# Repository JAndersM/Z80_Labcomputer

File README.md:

# Z80_Labcomputer

A computerproject based on the Z80 CPU.

## Dator
Motherboard with Z80, 8 kB ROM and 32 kB SRAM, IO ports, Bus ports etc.
* Schema, PCB designed
* Produced and tested. OK so far...

## cpukontroll
Clock, Reset etc.
* Schema, PCB design

## display
7x4-segment display and IO-connections to adress 0-3
* Schema PCB design

## tangentbord
Hex values input keyboard
* Schema, PCB design
Needs redesign

## EEPROMprogrammer
Arduino code and design for an Arduino Nano (or similar) based EEPROMprogrammer
* Schema, PCB design
Connected to the computer using BUSRQ to facilitate programming without removing ROM.

## simulering
Python simulation of the z80 cpu and the computer
* Inkludes 7x4 display
Many opcodes not simulated yet

## fastplatta
Holder for the Dator PCB
* 3D printed and tested

## Used software:
KiCad, FreeCAD, Python, Arduino IDE

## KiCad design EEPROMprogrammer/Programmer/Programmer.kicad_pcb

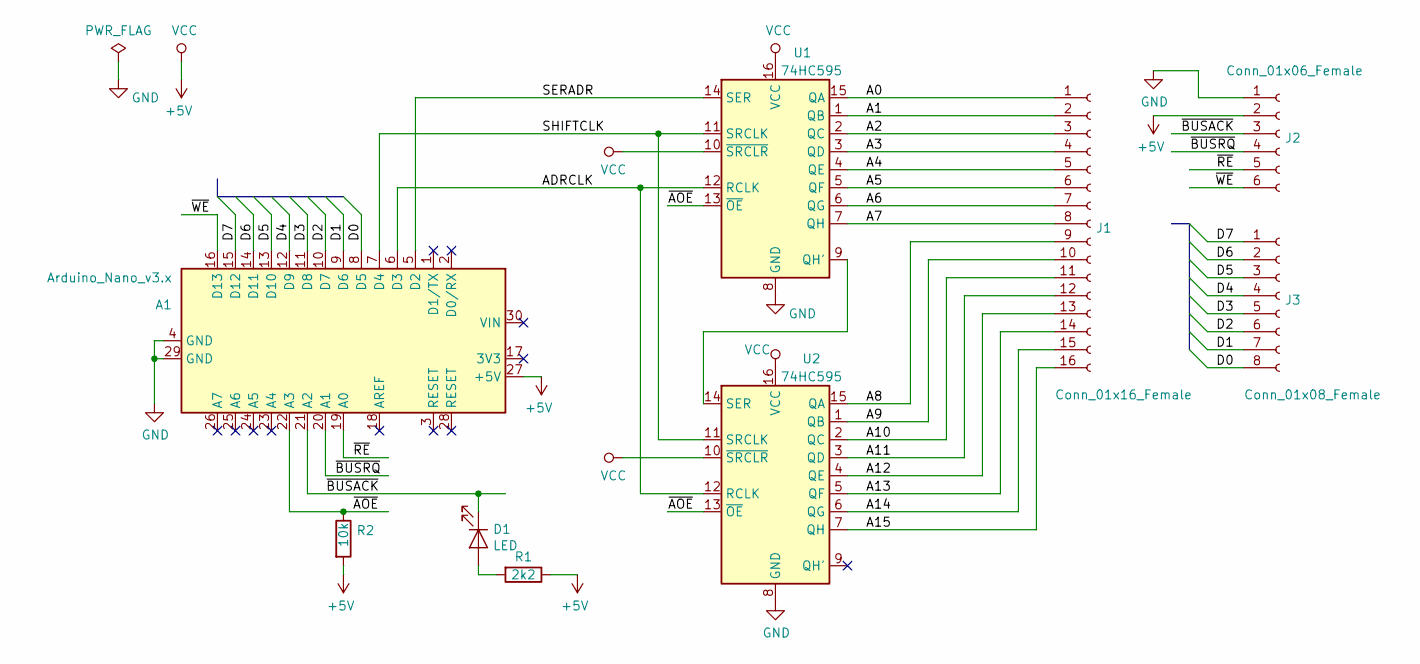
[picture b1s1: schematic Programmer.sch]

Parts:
A1: Arduino_Nano_v3.x; Arduino_Nano
D1: LED; LED_D3.0mm
J1: Conn_01x16_Female; PinSocket_1x16_P2.54mm_Vertical
J2: Conn_01x06_Female; PinSocket_1x06_P2.54mm_Vertical
J3: Conn_01x08_Female; PinSocket_1x08_P2.54mm_Vertical
R1: 2k2; R_Axial_DIN0207_L6.3mm_D2.5mm_P7.62mm_Horizontal
R2: 10k; R_Axial_DIN0207_L6.3mm_D2.5mm_P7.62mm_Horizontal
U1, U2: 74HC595; DIP-16_W7.62mm

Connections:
+5V: A1.27 (+5V), J2.2, R1.1, R2.2, U1.10 (~SRCLR), U1.16 (VCC), U2.10 (~SRCLR), U2.16 (VCC)
/A0: J1.1, U1.15 (QA)
/A1: J1.2, U1.1 (QB)
/A2: J1.3, U1.2 (QC)
/A3: J1.4, U1.3 (QD)
/A4: J1.5, U1.4 (QE)
/A5: J1.6, U1.5 (QF)
/A6: J1.7, U1.6 (QG)
/A7: J1.8, U1.7 (QH)
/A8: J1.9, U2.15 (QA)
/A9: J1.10, U2.1 (QB)
/A10: J1.11, U2.2 (QC)
/A11: J1.12, U2.3 (QD)
/A12: J1.13, U2.4 (QE)
/A13: J1.14, U2.5 (QF)
/A14: J1.15, U2.6 (QG)
/A15: J1.16, U2.7 (QH)
/ADRCLK: A1.6 (D3), U1.12 (RCLK), U2.12 (RCLK)
/D0: A1.8 (D5), J3.8
/D1: A1.9 (D6), J3.7
/D2: A1.10 (D7), J3.6
/D3: A1.11 (D8), J3.5
/D4: A1.12 (D9), J3.4
/D5: A1.13 (D10), J3.3
/D6: A1.14 (D11), J3.2
/D7: A1.15 (D12), J3.1
/SERADR: A1.5 (D2), U1.14 (SER)
/SHIFTCLK: A1.7 (D4), U1.11 (SRCLK), U2.11 (SRCLK)
/~AOE: A1.22 (A3), R2.1, U1.13 (~OE), U2.13 (~OE)
/~BUSACK: A1.21 (A2), D1.1 (K), J2.3
/~BUSRQ: A1.20 (A1), J2.4
/~RE: A1.19 (A0), J2.5
/~WE: A1.16 (D13), J2.6
GND: A1.4 (GND), A1.29 (GND), J2.1, U1.8 (GND), U2.8 (GND)
unnamed: D1.2 (A), R1.2
unnamed: U1.9 (QH'), U2.14 (SER)

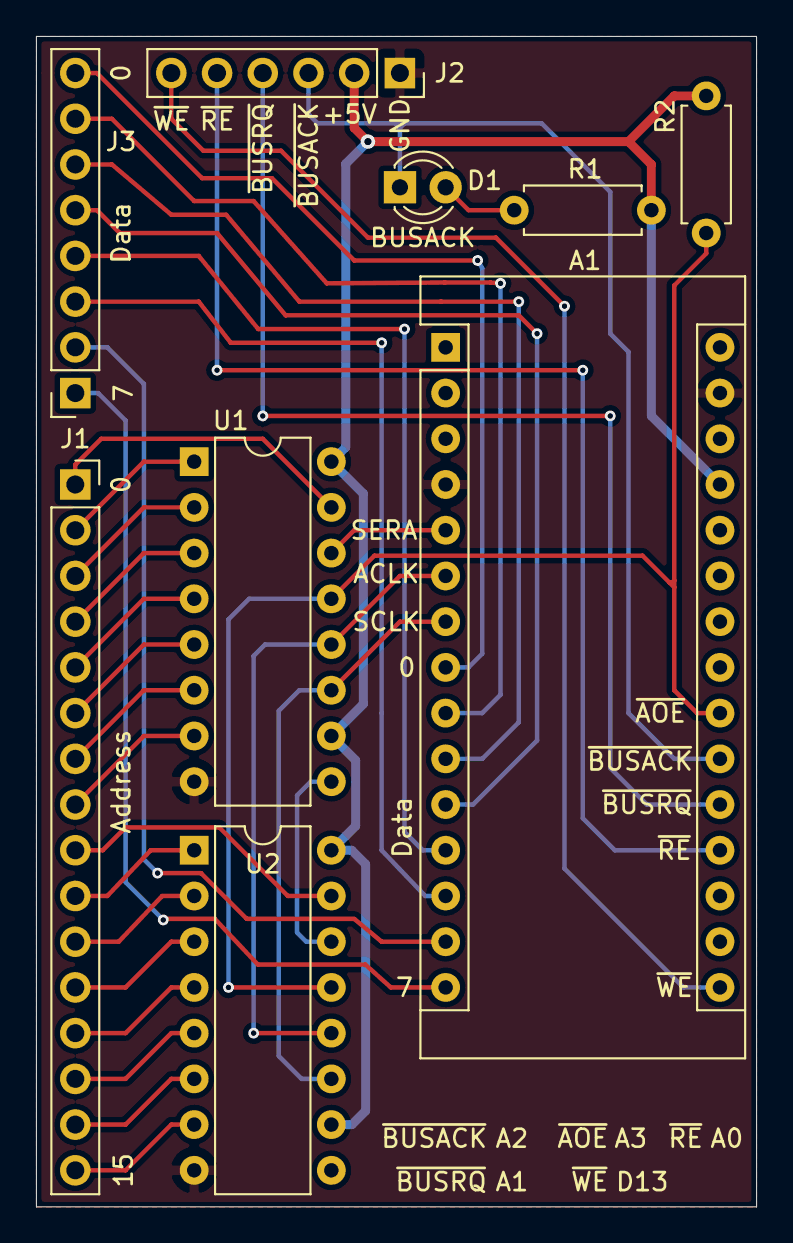
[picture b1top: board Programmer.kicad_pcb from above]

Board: 2 copper layers, 40.0 x 65.0 mm, 9 parts (0 on the bottom side), 36 nets.

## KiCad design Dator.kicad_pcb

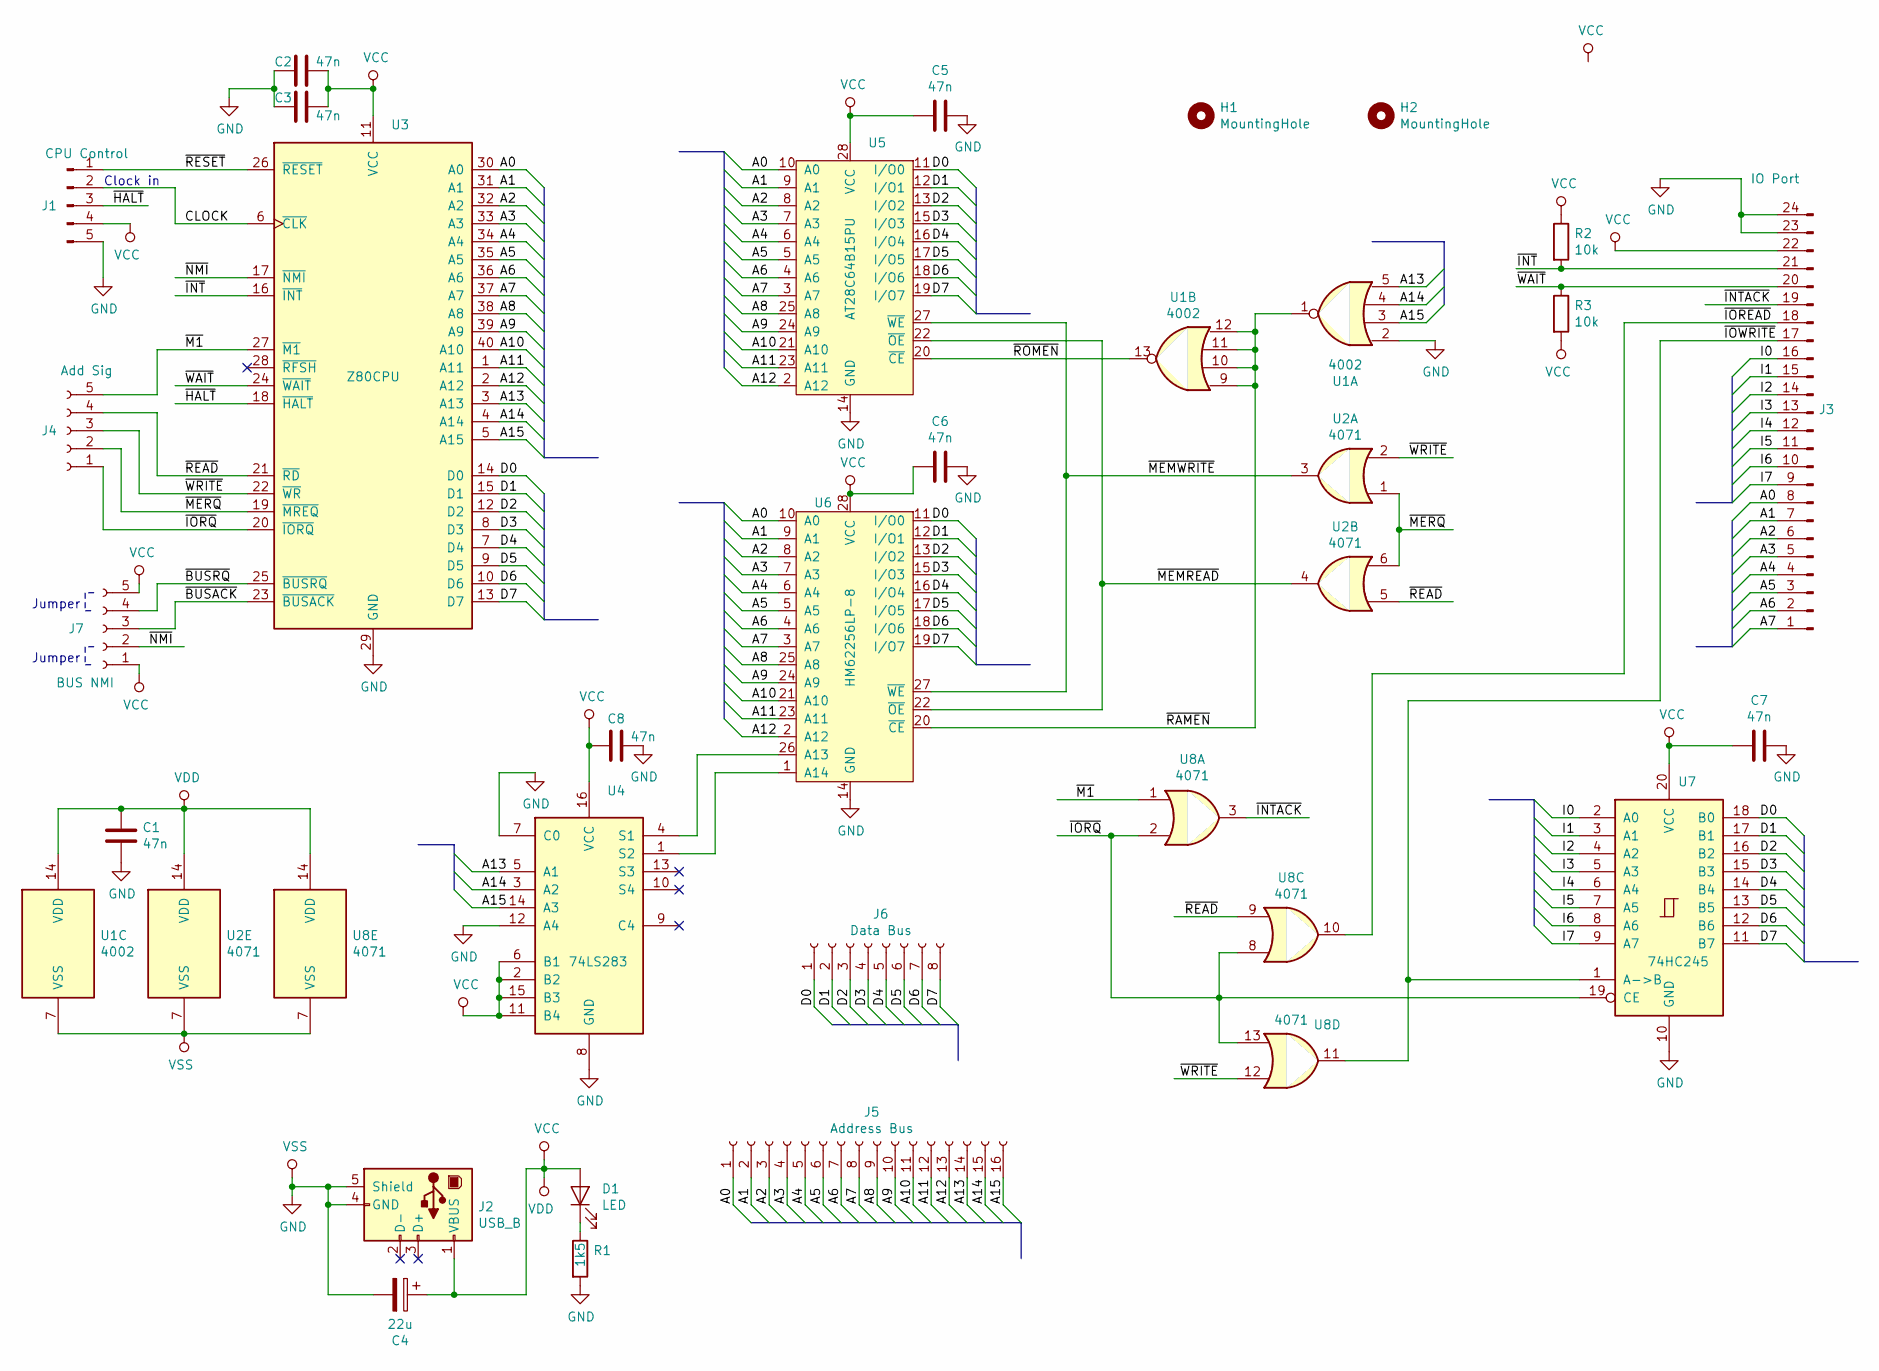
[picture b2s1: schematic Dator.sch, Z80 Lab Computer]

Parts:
C1, C2, C3, C5, C6, C7, C8: 47n; C_Disc_D3.0mm_W1.6mm_P2.50mm
C4: 22u; C_Radial_D5.0mm_H11.0mm_P2.00mm
D1: LED; LED_D3.0mm
H1, H2: MountingHole; MountingHole_2.2mm_M2
J1: CPU Control; PinHeader_1x05_P2.54mm_Vertical
J2: USB_B; USB_B_OST_USB-B1HSxx_Horizontal
J3: IO Port; PinHeader_1x24_P2.54mm_Vertical
J4: Add Sig; PinSocket_1x05_P2.54mm_Vertical
J5: Address Bus; PinSocket_1x16_P2.54mm_Vertical
J6: Data Bus; PinSocket_1x08_P2.54mm_Vertical
J7: BUS NMI; PinSocket_1x05_P2.54mm_Vertical
R1: 1k5; R_Axial_DIN0207_L6.3mm_D2.5mm_P7.62mm_Horizontal
R2, R3: 10k; R_Axial_DIN0207_L6.3mm_D2.5mm_P7.62mm_Horizontal
U1: 4002; DIP-14_W7.62mm
U2, U8: 4071; DIP-14_W7.62mm
U3: Z80CPU; DIP-40_W15.24mm_Socket
U4: 74LS283; DIP-16_W7.62mm
U5: AT28C64B15PU; DIP-28_W15.24mm_Socket
U6: HM62256LP-8; DIP-28_W15.24mm_Socket
U7: 74HC245; DIP-20_W7.62mm

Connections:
/A0: J3.8, J5.1, U3.30 (A0), U5.10 (A0), U6.10 (A0)
/A1: J3.7, J5.2, U3.31 (A1), U5.9 (A1), U6.9 (A1)
/A2: J3.6, J5.3, U3.32 (A2), U5.8 (A2), U6.8 (A2)
/A3: J3.5, J5.4, U3.33 (A3), U5.7 (A3), U6.7 (A3)
/A4: J3.4, J5.5, U3.34 (A4), U5.6 (A4), U6.6 (A4)
/A5: J3.3, J5.6, U3.35 (A5), U5.5 (A5), U6.5 (A5)
/A6: J3.2, J5.7, U3.36 (A6), U5.4 (A6), U6.4 (A6)
/A7: J3.1, J5.8, U3.37 (A7), U5.3 (A7), U6.3 (A7)
/A8: J5.9, U3.38 (A8), U5.25 (A8), U6.25 (A8)
/A9: J5.10, U3.39 (A9), U5.24 (A9), U6.24 (A9)
/A10: J5.11, U3.40 (A10), U5.21 (A10), U6.21 (A10)
/A11: J5.12, U3.1 (A11), U5.23 (A11), U6.23 (A11)
/A12: J5.13, U3.2 (A12), U5.2 (A12), U6.2 (A12)
/A13: J5.14, U1.5, U3.3 (A13), U4.5 (A1)
/A14: J5.15, U1.4, U3.4 (A14), U4.3 (A2)
/A15: J5.16, U1.3, U3.5 (A15), U4.14 (A3)
/CLOCK: J1.2, U3.6 (~CLK~)
/D0: J6.1, U3.14 (D0), U5.11 (I/O0), U6.11 (I/O0), U7.18 (B0)
/D1: J6.2, U3.15 (D1), U5.12 (I/O1), U6.12 (I/O1), U7.17 (B1)
/D2: J6.3, U3.12 (D2), U5.13 (I/O2), U6.13 (I/O2), U7.16 (B2)
/D3: J6.4, U3.8 (D3), U5.15 (I/O3), U6.15 (I/O3), U7.15 (B3)
/D4: J6.5, U3.7 (D4), U5.16 (I/O4), U6.16 (I/O4), U7.14 (B4)
/D5: J6.6, U3.9 (D5), U5.17 (I/O5), U6.17 (I/O5), U7.13 (B5)
/D6: J6.7, U3.10 (D6), U5.18 (I/O6), U6.18 (I/O6), U7.12 (B6)
/D7: J6.8, U3.13 (D7), U5.19 (I/O7), U6.19 (I/O7), U7.11 (B7)
/I0: J3.16, U7.2 (A0)
/I1: J3.15, U7.3 (A1)
/I2: J3.14, U7.4 (A2)
/I3: J3.13, U7.5 (A3)
/I4: J3.12, U7.6 (A4)
/I5: J3.11, U7.7 (A5)
/I6: J3.10, U7.8 (A6)
/I7: J3.9, U7.9 (A7)
/~BUSACK: J7.3, U3.23 (~BUSACK~)
/~BUSRQ: J7.4, U3.25 (~BUSRQ~)
/~HALT: J1.3, U3.18 (~HALT~)
/~INT: J3.21, R2.2, U3.16 (~INT~)
/~INTACK: J3.19, U8.3
/~IOREAD: J3.18, U8.10
/~IORQ: J4.1, U3.20 (~IORQ~), U7.19 (CE), U8.2, U8.8, U8.13
/~IOWRITE: J3.17, U7.1 (A->B), U8.11
/~M1: J4.5, U3.27 (~M1~), U8.1
/~MEMREAD: U2.4, U5.22 (~OE), U6.22 (~OE)
/~MEMWRITE: U2.3, U5.27 (~WE), U6.27 (~WE)
/~MERQ: J4.2, U2.1, U2.6, U3.19 (~MREQ~)
/~NMI: J7.2, U3.17 (~NMI~)
/~RAMEN: U1.1, U1.9, U1.10, U1.11, U1.12, U6.20 (~CE)
/~READ: J4.4, U2.5, U3.21 (~RD~), U8.9
/~RESET: J1.1, U3.26 (~RESET~)
/~ROMEN: U1.13, U5.20 (~CE)
/~WAIT: J3.20, R3.1, U3.24 (~WAIT~)
/~WRITE: J4.3, U2.2, U3.22 (~WR~), U8.12
GND: C1.2, C2.2, C3.2, C4.2, C5.1, C6.1, C7.1, C8.1, J1.5, J2.4 (GND), J2.5 (Shield), J3.23, J3.24, R1.2, U1.2, U1.7 (VSS), U2.7 (VSS), U3.29 (GND), U4.7 (C0), U4.8 (GND), U4.12 (A4), U5.14 (GND), U6.14 (GND), U7.10 (GND), U8.7 (VSS)
unnamed: D1.1 (K), R1.1
unnamed: U4.1 (S2), U6.1 (A14)
unnamed: U4.4 (S1), U6.26 (A13)
VCC: C1.1, C2.1, C3.1, C4.1, C5.2, C6.2, C7.2, C8.2, D1.2 (A), J1.4, J2.1 (VBUS), J3.22, J7.1, J7.5, R2.1, R3.2, U1.14 (VDD), U2.14 (VDD), U3.11 (VCC), U4.2 (B2), U4.6 (B1), U4.11 (B4), U4.15 (B3), U4.16 (VCC), U5.28 (VCC), U6.28 (VCC), U7.20 (VCC), U8.14 (VDD)

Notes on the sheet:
Clock in
Jumper

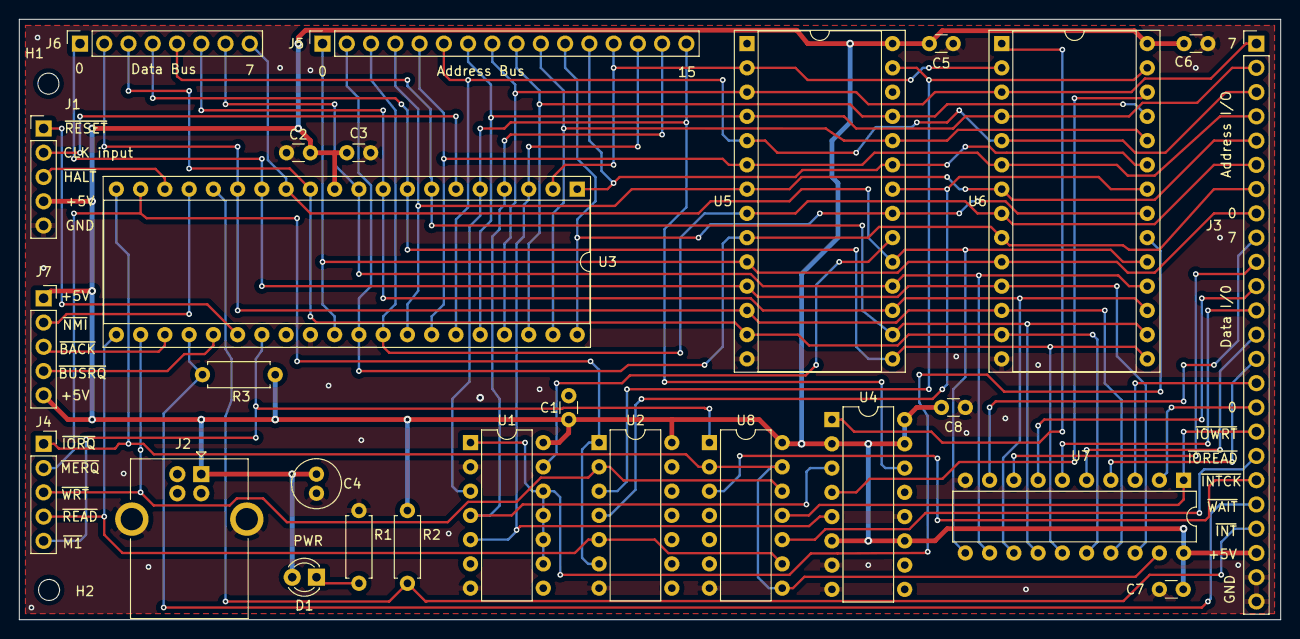
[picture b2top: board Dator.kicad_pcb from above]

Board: 2 copper layers, 132.1 x 62.9 mm, 29 parts (0 on the bottom side), 57 nets.

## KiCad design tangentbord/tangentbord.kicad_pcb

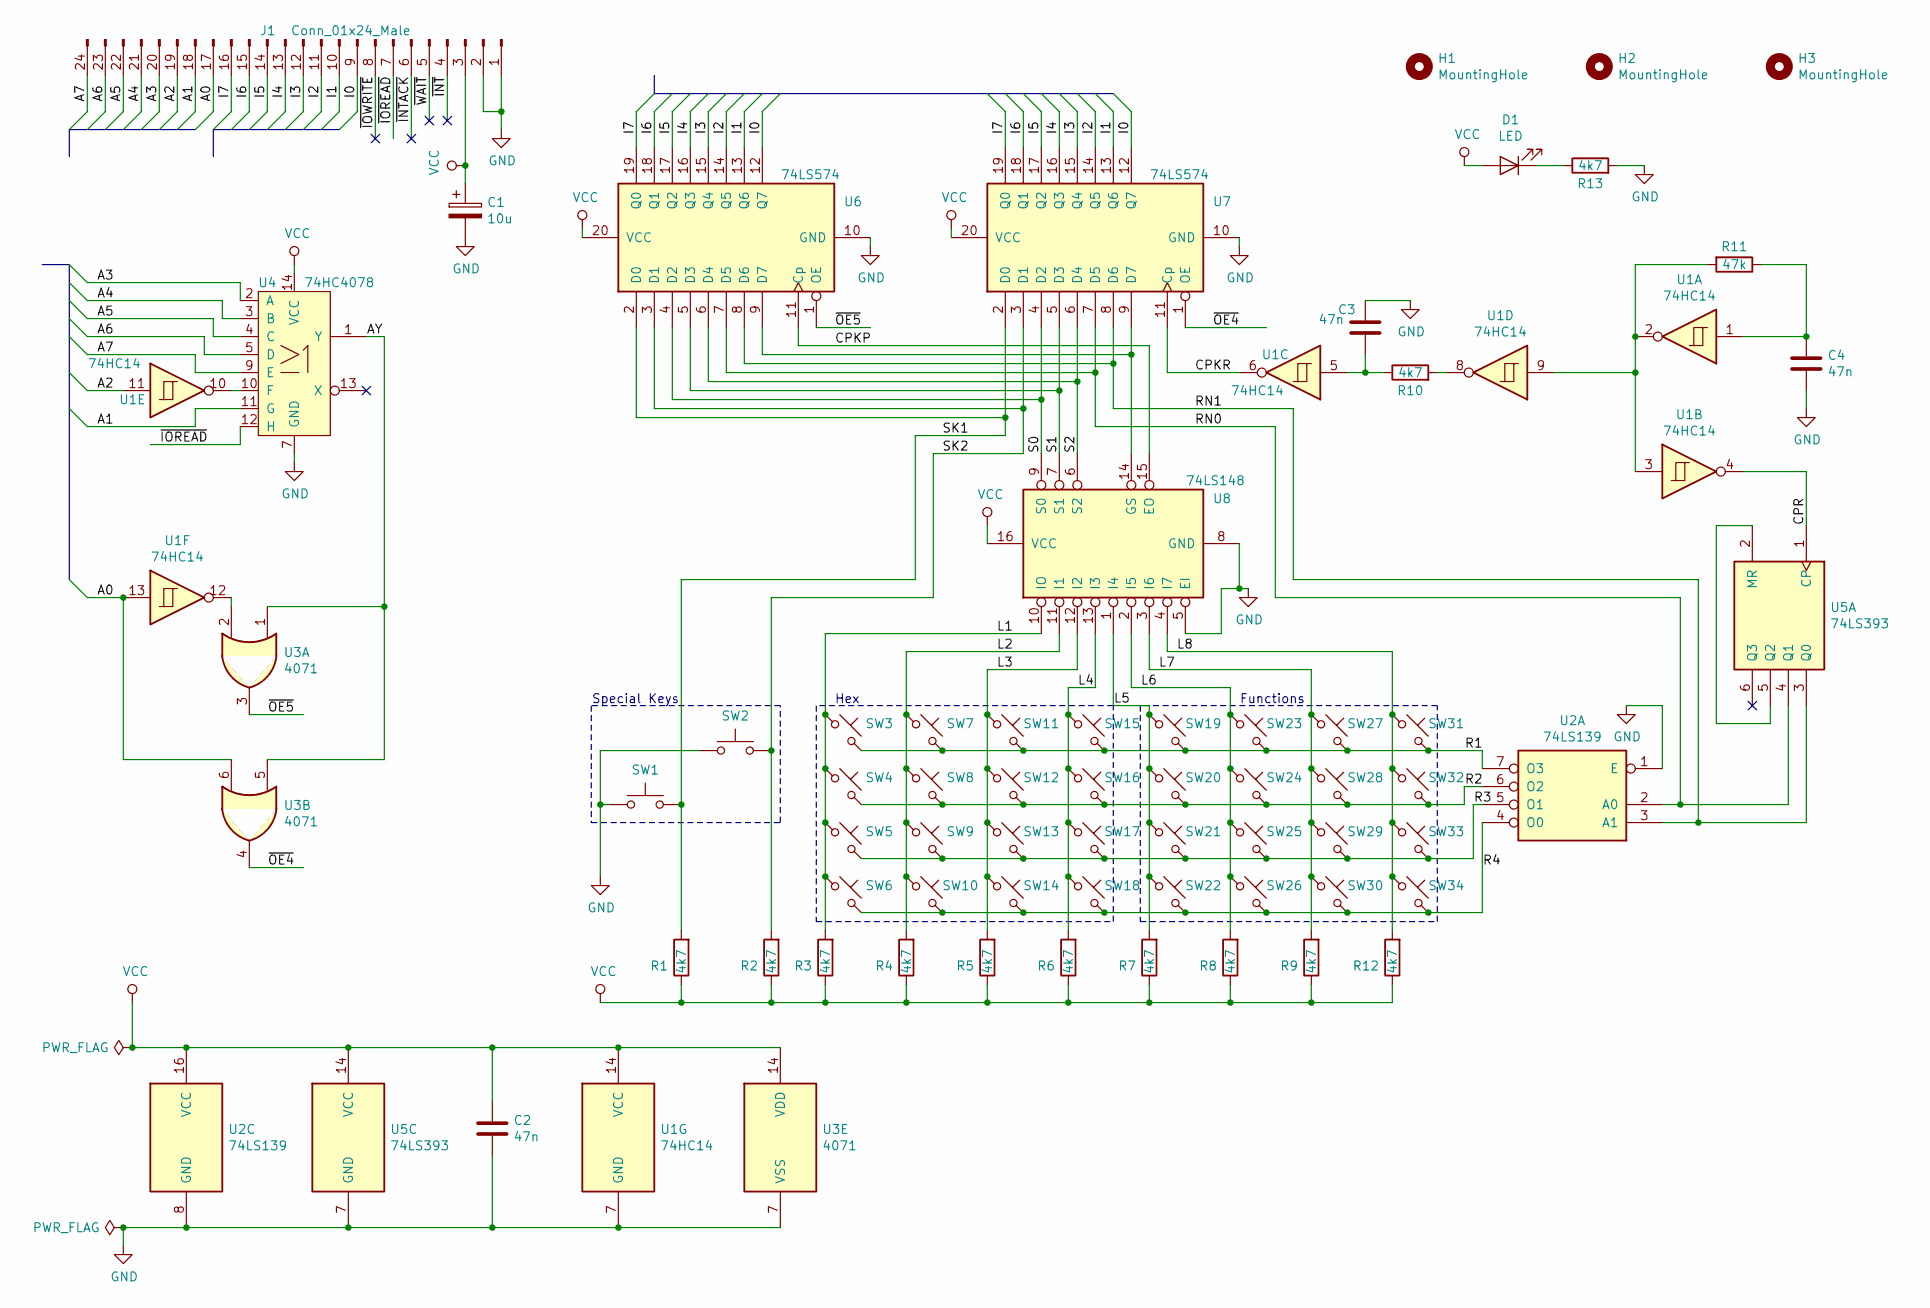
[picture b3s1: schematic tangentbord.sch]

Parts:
C1: 10u; CP_Radial_D5.0mm_P2.00mm
C2, C3, C4: 47n; C_Disc_D3.0mm_W2.0mm_P2.50mm
D1: LED; LED_D3.0mm
H1, H2, H3: MountingHole; MountingHole_2.2mm_M2
J1: Conn_01x24_Male; PinHeader_1x24_P2.54mm_Vertical
R1, R2, R3, R4, R5, R6, R7, R8, R9, R10, R12, R13: 4k7; R_Axial_DIN0207_L6.3mm_D2.5mm_P7.62mm_Horizontal
R11: 47k; R_Axial_DIN0207_L6.3mm_D2.5mm_P7.62mm_Horizontal
SW1, SW2: SW_Push; SW_PUSH_6mm
SW3, SW4, SW5, SW6, SW7, SW8, SW9, SW10, SW11, SW12, SW13, SW14, SW15, SW16, SW17, SW18, SW19, SW20, SW21, SW22, SW23, SW24, SW25, SW26, SW27, SW28, SW29, SW30, SW31, SW32, SW33, SW34: SW_Push_45deg; SW_PUSH_6mm
U1: 74HC14; DIP-14_W7.62mm
U2: 74LS139; DIP-16_W7.62mm
U3: 4071; DIP-14_W7.62mm
U4: 74HC4078; DIP-14_W7.62mm
U5: 74LS393; DIP-14_W7.62mm
U6, U7: 74LS574; DIP-20_W7.62mm
U8: 74LS148; DIP-16_W7.62mm

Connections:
/A0: J1.17, U1.13, U3.6
/A1: J1.18, U4.11 (G)
/A2: J1.19, U1.11
/A3: J1.20, U4.2 (A)
/A4: J1.21, U4.3 (B)
/A5: J1.22, U4.4 (C)
/A6: J1.23, U4.5 (D)
/A7: J1.24, U4.9 (E)
/AY: U3.1, U3.5, U4.1 (Y)
/CPKP: U6.11 (Cp), U8.15 (EO)
/CPKR: U1.6, U7.11 (Cp)
/CPR: U1.4, U5.1 (CP)
/I0: J1.9, U6.12 (Q7), U7.12 (Q7)
/I1: J1.10, U6.13 (Q6), U7.13 (Q6)
/I2: J1.11, U6.14 (Q5), U7.14 (Q5)
/I3: J1.12, U6.15 (Q4), U7.15 (Q4)
/I4: J1.13, U6.16 (Q3), U7.16 (Q3)
/I5: J1.14, U6.17 (Q2), U7.17 (Q2)
/I6: J1.15, U6.18 (Q1), U7.18 (Q1)
/I7: J1.16, U6.19 (Q0), U7.19 (Q0)
/L1: R3.2, SW3.1, SW4.1, SW5.1, SW6.1, U8.10 (IO)
/L2: R4.2, SW7.1, SW8.1, SW9.1, SW10.1, U8.11 (I1)
/L3: R5.2, SW11.1, SW12.1, SW13.1, SW14.1, U8.12 (I2)
/L4: R6.2, SW15.1, SW16.1, SW17.1, SW18.1, U8.13 (I3)
/L5: R7.2, SW19.1, SW20.1, SW21.1, SW22.1, U8.1 (I4)
/L6: R8.2, SW23.1, SW24.1, SW25.1, SW26.1, U8.2 (I5)
/L7: R9.2, SW27.1, SW28.1, SW29.1, SW30.1, U8.3 (I6)
/L8: R12.2, SW31.1, SW32.1, SW33.1, SW34.1, U8.4 (I7)
/R1: SW3.2, SW7.2, SW11.2, SW15.2, SW19.2, SW23.2, SW27.2, SW31.2, U2.7 (O3)
/R2: SW4.2, SW8.2, SW12.2, SW16.2, SW20.2, SW24.2, SW28.2, SW32.2, U2.6 (O2)
/R3: SW5.2, SW9.2, SW13.2, SW17.2, SW21.2, SW25.2, SW29.2, SW33.2, U2.5 (O1)
/R4: SW6.2, SW10.2, SW14.2, SW18.2, SW22.2, SW26.2, SW30.2, SW34.2, U2.4 (O0)
/RN0: U2.2 (A0), U5.4 (Q1), U6.7 (D5), U7.7 (D5)
/RN1: U2.3 (A1), U5.3 (Q0), U6.8 (D6), U7.8 (D6)
/S0: U6.4 (D2), U7.4 (D2), U8.9 (S0)
/S1: U6.5 (D3), U7.5 (D3), U8.7 (S1)
/S2: U6.6 (D4), U7.6 (D4), U8.6 (S2)
/SK1: R1.2, SW1.2, U6.2 (D0), U7.2 (D0)
/SK2: R2.2, SW2.2, U6.3 (D1), U7.3 (D1)
/~INT: J1.4
/~INTACK: J1.6
/~IOREAD: J1.7, U4.12 (H)
/~IOWRITE: J1.8
/~OE4: U3.4, U7.1 (OE)
/~OE5: U3.3, U6.1 (OE)
/~WAIT: J1.5
GND: C1.2, C2.2, C3.2, C4.2, J1.1, J1.2, R13.2, SW1.1, SW2.1, U1.7 (GND), U2.1 (E), U2.8 (GND), U3.7 (VSS), U4.7 (GND), U5.7 (GND), U6.10 (GND), U7.10 (GND), U8.5 (EI), U8.8 (GND)
unnamed: C3.1, R10.1, U1.5
unnamed: C4.1, R11.1, U1.1
unnamed: D1.1 (K), R13.1
unnamed: R10.2, U1.8
unnamed: R11.2, U1.2, U1.3, U1.9
unnamed: U1.10, U4.10 (F)
unnamed: U1.12, U3.2
unnamed: U5.2 (MR), U5.5 (Q2)
unnamed: U6.9 (D7), U7.9 (D7), U8.14 (GS)
VCC: C1.1, C2.1, D1.2 (A), J1.3, R1.1, R2.1, R3.1, R4.1, R5.1, R6.1, R7.1, R8.1, R9.1, R12.1, U1.14 (VCC), U2.16 (VCC), U3.14 (VDD), U4.14 (VCC), U5.14 (VCC), U6.20 (VCC), U7.20 (VCC), U8.16 (VCC)

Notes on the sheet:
Special Keys
Hex
Functions

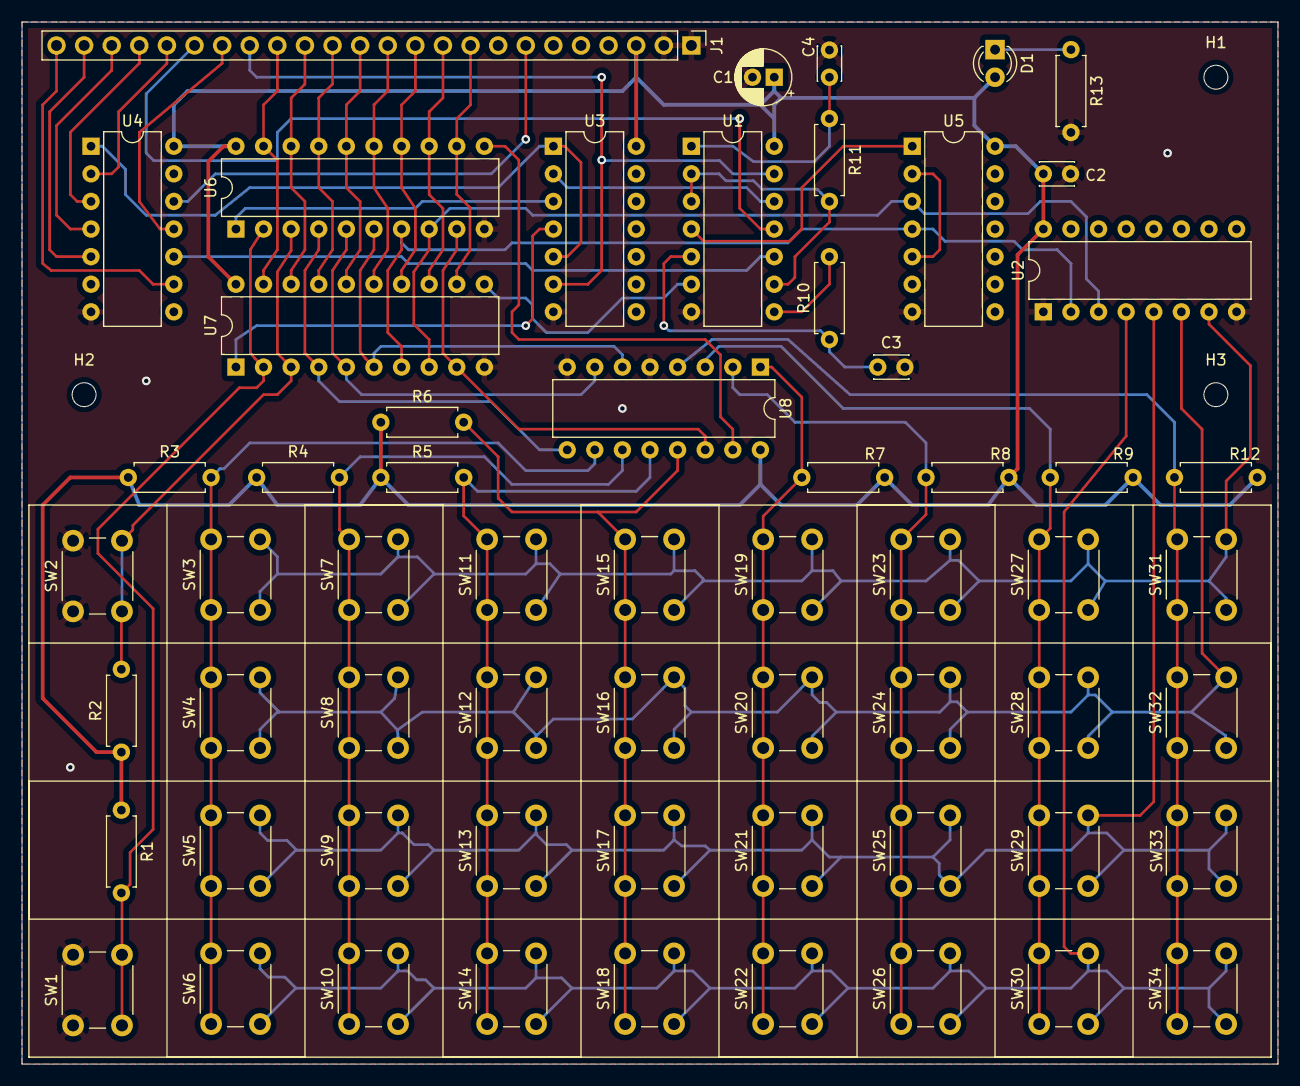
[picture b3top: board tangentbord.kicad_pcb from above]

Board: 2 copper layers, 115.6 x 95.9 mm, 64 parts (0 on the bottom side), 53 nets.

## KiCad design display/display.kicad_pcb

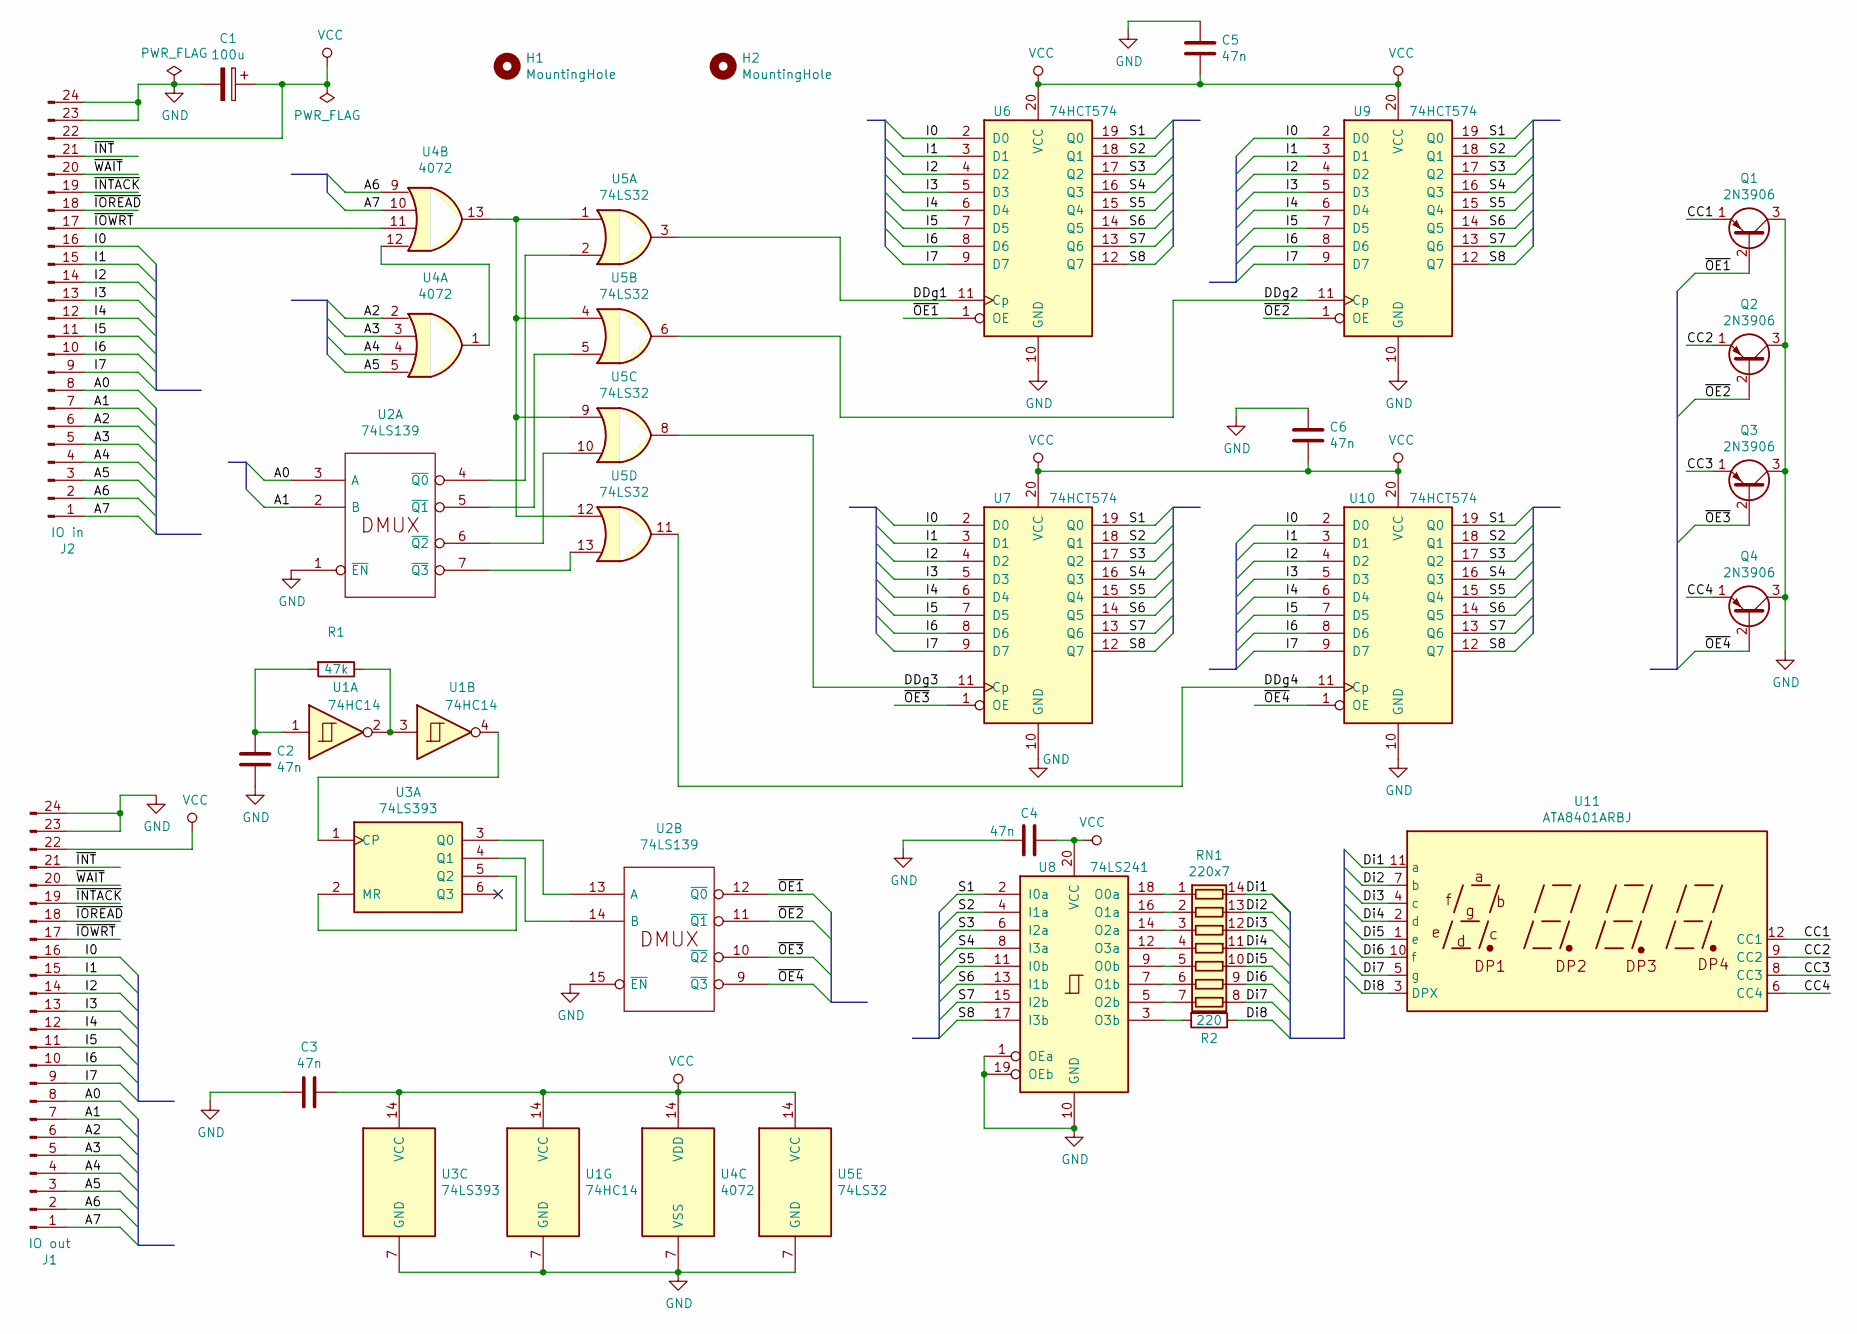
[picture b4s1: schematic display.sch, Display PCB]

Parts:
C1: 100u; CP_Radial_D6.3mm_P2.50mm
C2, C3, C4, C5, C6: 47n; C_Disc_D3.0mm_W1.6mm_P2.50mm
H1, H2: MountingHole; MountingHole_2.2mm_M2
J1: IO out; PinHeader_1x24_P2.54mm_Vertical
J2: IO in; PinHeader_1x24_P2.54mm_Vertical
Q1, Q2, Q3, Q4: 2N3906; TO-92L_Inline_Wide
R1: 47k; R_Axial_DIN0207_L6.3mm_D2.5mm_P7.62mm_Horizontal
R2: 220; R_Axial_DIN0207_L6.3mm_D2.5mm_P7.62mm_Horizontal
RN1: 220x7; DIP-14_W7.62mm
U1: 74HC14; DIP-14_W7.62mm
U2: 74LS139; DIP-16_W7.62mm
U3: 74LS393; DIP-14_W7.62mm
U4: 4072; DIP-14_W7.62mm
U5: 74LS32; DIP-14_W7.62mm
U6, U7, U9, U10: 74HCT574; DIP-20_W7.62mm
U8: 74LS241; DIP-20_W7.62mm
U11: ATA8401ARBJ

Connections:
/A0: J1.8, J2.8, U2.3 (A)
/A1: J1.7, J2.7, U2.2 (B)
/A2: J1.6, J2.6, U4.2
/A3: J1.5, J2.5, U4.3
/A4: J1.4, J2.4, U4.4
/A5: J1.3, J2.3, U4.5
/A6: J1.2, J2.2, U4.9
/A7: J1.1, J2.1, U4.10
/CC1: Q1.1 (E), U11.12 (CC1)
/CC2: Q2.1 (E), U11.9 (CC2)
/CC3: Q3.1 (E), U11.8 (CC3)
/CC4: Q4.1 (E), U11.6 (CC4)
/DDg1: U5.3, U6.11 (Cp)
/DDg2: U5.6, U9.11 (Cp)
/DDg3: U5.8, U7.11 (Cp)
/DDg4: U5.11, U10.11 (Cp)
/Di1: RN1.14 (R1.2), U11.11 (a)
/Di2: RN1.13 (R2.2), U11.7 (b)
/Di3: RN1.12 (R3.2), U11.4 (c)
/Di4: RN1.11 (R4.2), U11.2 (d)
/Di5: RN1.10 (R5.2), U11.1 (e)
/Di6: RN1.9 (R6.2), U11.10 (f)
/Di7: RN1.8 (R7.2), U11.5 (g)
/Di8: R2.1, U11.3 (DPX)
/I0: J1.16, J2.16, U6.2 (D0), U7.2 (D0), U9.2 (D0), U10.2 (D0)
/I1: J1.15, J2.15, U6.3 (D1), U7.3 (D1), U9.3 (D1), U10.3 (D1)
/I2: J1.14, J2.14, U6.4 (D2), U7.4 (D2), U9.4 (D2), U10.4 (D2)
/I3: J1.13, J2.13, U6.5 (D3), U7.5 (D3), U9.5 (D3), U10.5 (D3)
/I4: J1.12, J2.12, U6.6 (D4), U7.6 (D4), U9.6 (D4), U10.6 (D4)
/I5: J1.11, J2.11, U6.7 (D5), U7.7 (D5), U9.7 (D5), U10.7 (D5)
/I6: J1.10, J2.10, U6.8 (D6), U7.8 (D6), U9.8 (D6), U10.8 (D6)
/I7: J1.9, J2.9, U6.9 (D7), U7.9 (D7), U9.9 (D7), U10.9 (D7)
/S1: U6.19 (Q0), U7.19 (Q0), U8.2 (I0a), U9.19 (Q0), U10.19 (Q0)
/S2: U6.18 (Q1), U7.18 (Q1), U8.4 (I1a), U9.18 (Q1), U10.18 (Q1)
/S3: U6.17 (Q2), U7.17 (Q2), U8.6 (I2a), U9.17 (Q2), U10.17 (Q2)
/S4: U6.16 (Q3), U7.16 (Q3), U8.8 (I3a), U9.16 (Q3), U10.16 (Q3)
/S5: U6.15 (Q4), U7.15 (Q4), U8.11 (I0b), U9.15 (Q4), U10.15 (Q4)
/S6: U6.14 (Q5), U7.14 (Q5), U8.13 (I1b), U9.14 (Q5), U10.14 (Q5)
/S7: U6.13 (Q6), U7.13 (Q6), U8.15 (I2b), U9.13 (Q6), U10.13 (Q6)
/S8: U6.12 (Q7), U7.12 (Q7), U8.17 (I3b), U9.12 (Q7), U10.12 (Q7)
/~INT: J1.21, J2.21
/~INTACK: J1.19, J2.19
/~IOREAD: J1.18, J2.18
/~IOWRT: J1.17, J2.17, U4.11
/~OE1: Q1.2 (B), U2.12 (~Q0), U6.1 (OE)
/~OE2: Q2.2 (B), U2.11 (~Q1), U9.1 (OE)
/~OE3: Q3.2 (B), U2.10 (~Q2), U7.1 (OE)
/~OE4: Q4.2 (B), U2.9 (~Q3), U10.1 (OE)
/~WAIT: J1.20, J2.20
GND: C1.2, C2.1, C3.2, C4.2, C5.1, C6.1, J1.23, J1.24, J2.23, J2.24, Q1.3 (C), Q2.3 (C), Q3.3 (C), Q4.3 (C), U1.7 (GND), U2.1 (~EN), U2.8 (GND), U2.15 (~EN), U3.7 (GND), U4.7 (VSS), U5.7 (GND), U6.10 (GND), U7.10 (GND), U8.1 (OEa), U8.10 (GND), U8.19 (OEb), U9.10 (GND), U10.10 (GND)
unnamed: C2.2, R1.2, U1.1
unnamed: R1.1, U1.2, U1.3
unnamed: R2.2, U8.3 (O3b)
unnamed: RN1.1 (R1.1), U8.18 (O0a)
unnamed: RN1.2 (R2.1), U8.16 (O1a)
unnamed: RN1.3 (R3.1), U8.14 (O2a)
unnamed: RN1.4 (R4.1), U8.12 (O3a)
unnamed: RN1.5 (R5.1), U8.9 (O0b)
unnamed: RN1.6 (R6.1), U8.7 (O1b)
unnamed: RN1.7 (R7.1), U8.5 (O2b)
unnamed: U1.4, U3.1 (CP)
unnamed: U2.4 (~Q0), U5.2
unnamed: U2.5 (~Q1), U5.5
unnamed: U2.6 (~Q2), U5.10
unnamed: U2.7 (~Q3), U5.13
unnamed: U2.13 (A), U3.3 (Q0)
unnamed: U2.14 (B), U3.4 (Q1)
unnamed: U3.2 (MR), U3.5 (Q2)
unnamed: U4.1, U4.12
unnamed: U4.13, U5.1, U5.4, U5.9, U5.12
VCC: C1.1, C3.1, C4.1, C5.2, C6.2, J1.22, J2.22, U1.14 (VCC), U2.16 (VCC), U3.14 (VCC), U4.14 (VDD), U5.14 (VCC), U6.20 (VCC), U7.20 (VCC), U8.20 (VCC), U9.20 (VCC), U10.20 (VCC)

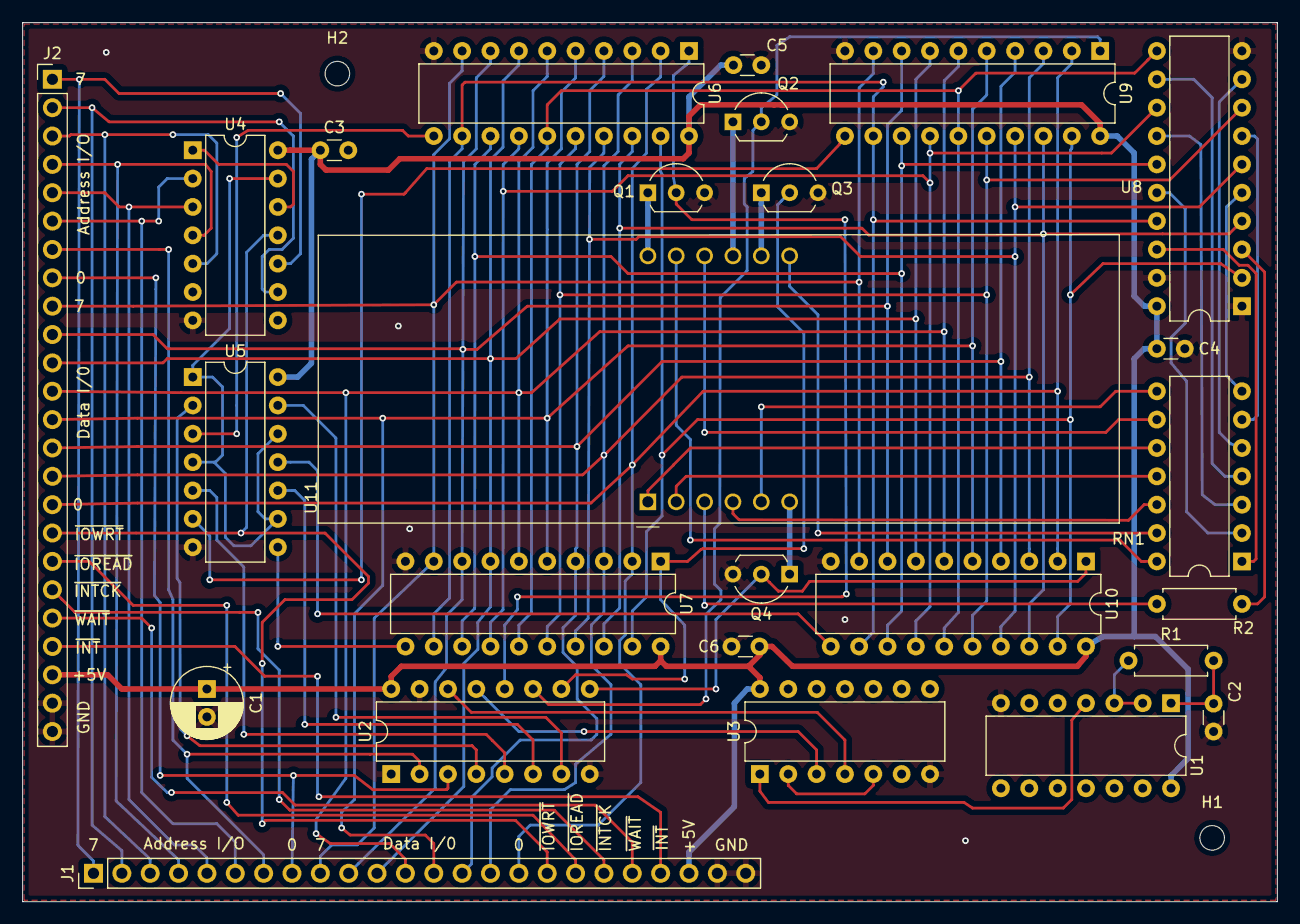
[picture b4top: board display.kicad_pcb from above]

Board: 2 copper layers, 112.4 x 78.7 mm, 28 parts (0 on the bottom side), 71 nets.

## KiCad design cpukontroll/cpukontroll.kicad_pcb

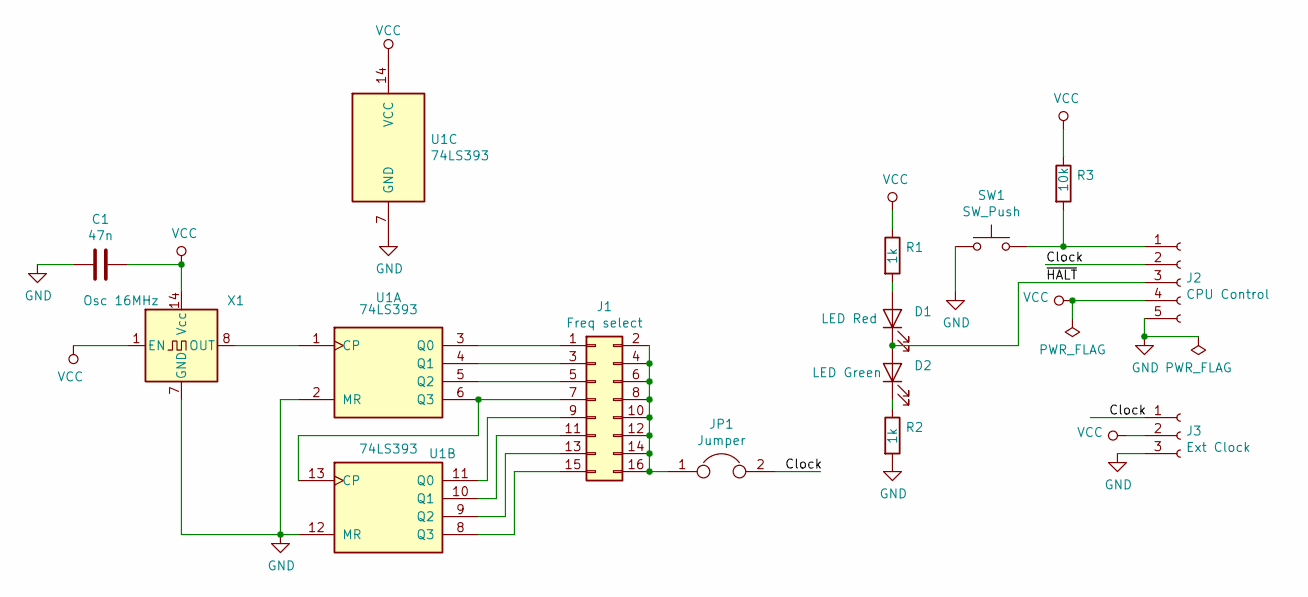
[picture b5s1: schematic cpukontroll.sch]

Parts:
C1: 47n; C_Disc_D3.0mm_W1.6mm_P2.50mm
D1: LED Red; LED_D3.0mm
D2: LED Green; LED_D3.0mm
J1: Freq select; PinSocket_2x08_P2.54mm_Vertical
J2: CPU Control; PinSocket_1x05_P2.54mm_Vertical
J3: Ext Clock; PinSocket_1x03_P2.54mm_Vertical
JP1: Jumper; PinHeader_1x02_P2.54mm_Vertical
R1, R2: 1k; R_Axial_DIN0207_L6.3mm_D2.5mm_P7.62mm_Horizontal
R3: 10k; R_Axial_DIN0207_L6.3mm_D2.5mm_P7.62mm_Horizontal
SW1: SW_Push; SW_PUSH_6mm
U1: 74LS393; DIP-14_W7.62mm
X1: Osc 16MHz; Oscillator_DIP-14

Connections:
/Clock: J2.2, J3.1, JP1.2
GND: C1.2, J2.5, J3.3, R2.2, SW1.1, U1.2 (MR), U1.7 (GND), U1.12 (MR), X1.7 (GND)
unnamed: D1.1 (K), D2.2 (A), J2.3
unnamed: D1.2 (A), R1.2
unnamed: D2.1 (K), R2.1
unnamed: J1.1, U1.3 (Q0)
unnamed: J1.3, U1.4 (Q1)
unnamed: J1.5, U1.5 (Q2)
unnamed: J1.7, U1.6 (Q3), U1.13 (CP)
unnamed: J1.9, U1.11 (Q0)
unnamed: J1.2, J1.4, J1.6, J1.8, J1.10, J1.12, J1.14, J1.16, JP1.1
unnamed: J1.11, U1.10 (Q1)
unnamed: J1.13, U1.9 (Q2)
unnamed: J1.15, U1.8 (Q3)
unnamed: J2.1, R3.2, SW1.2
unnamed: U1.1 (CP), X1.8 (OUT)
VCC: C1.1, J2.4, J3.2, R1.1, R3.1, U1.14 (VCC), X1.1 (EN), X1.14 (Vcc)

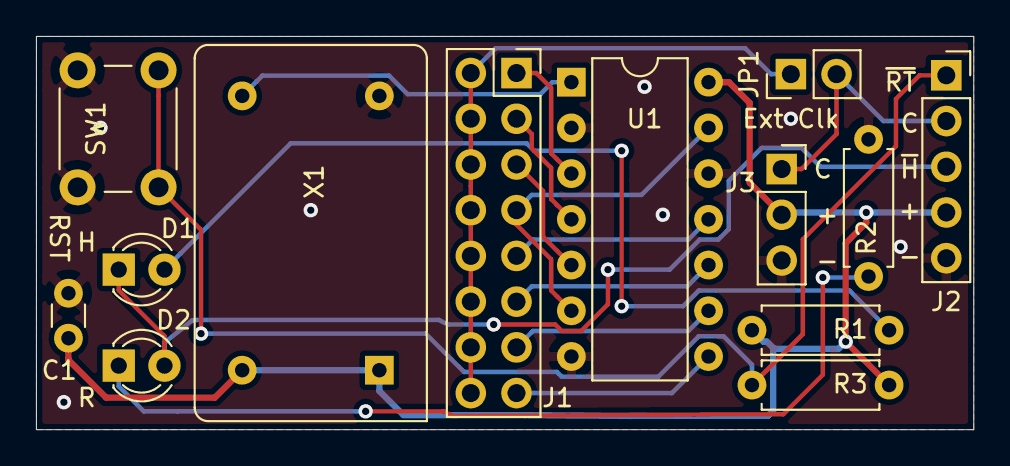
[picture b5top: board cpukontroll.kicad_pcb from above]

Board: 2 copper layers, 52.1 x 21.8 mm, 13 parts (0 on the bottom side), 17 nets.

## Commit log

2019-10-31 Start
2019-10-31 Display start
2019-10-31 More Display work
2019-11-02 lib cache added and display schema
2019-11-02 display schema first version ready
2019-11-02 display schema data files
2019-11-02 display tracks drawn
2019-11-03 display pcb first version ready
2019-11-09 started tangentbord
2019-11-10 Tangentbord pcb v1
2019-11-24 EEPROMprogrammerare
2019-12-13 EEPROMprogrammerare pcb
2020-02-19 pcb filer
2020-04-08 Frame for dator pcb
2020-04-09 Frame updated dim
2020-05-06 Python simulator
2020-05-09 Bugfixes and small test program
2020-05-11 Sim settings easier to spot/change
2020-05-19 Readme update, opcodes added
2020-05-22 In situ programming hw
2020-05-23 Pull up AOE
